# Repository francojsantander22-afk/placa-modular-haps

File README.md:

# main_board_habp

Placa principal (main board) del sistema de adquisición de datos y telemetría para un **globo meteorológico de alta altitud (HABP – High Altitude Balloon Project)**, diseñada en KiCad. Este repositorio contiene el esquemático, el PCB y los archivos de proyecto de la placa que integra el microcontrolador, la red de sensores, el módulo GPS, el enlace LoRa y el sistema de gestión de energía del nodo.

Este proyecto forma parte de una pasantía en CEGA Electrónica, desarrollada por **Franco Santander** y **Lisandro Elmelaj**.

## Descripción general

El objetivo del sistema es recolectar variables físicas del entorno y datos de posicionamiento durante el vuelo de un globo de alta altitud, empaquetarlos de forma eficiente y transmitirlos por radiofrecuencia mediante LoRa, todo en un nodo autónomo capaz de operar en condiciones extremas (hasta ~30 km de altitud, presión menor a 1 kPa y temperaturas de hasta -70 °C).

El sistema completo se organiza en cuatro subsistemas funcionales:

1. Red de sensores
2. Procesamiento de datos y empaquetado
3. Gestión de energía
4. Enlace de comunicaciones (LoRa)

## Hardware

### Microcontrolador

El núcleo del sistema es un microcontrolador de la familia **STM32** (STM32WL55C), montado sobre el módulo **Quectel KG200Z**, que integra de fábrica la etapa de radiofrecuencia LoRa.

### Red de sensores (bus I2C)

Todos los sensores se comunican por I2C (interfaz `I2C3`):

- **BMI270** – IMU de 6 grados de libertad (acelerómetro + giroscopio) con sensor de temperatura interno.
- **SHT21** – Temperatura y humedad ambiente.
- **MS5611** – Presión atmosférica absoluta y temperatura (cálculo de altitud redundante).
- **CMPS2** – Magnetómetro, orientación y azimut respecto al norte magnético.

### Posicionamiento y depuración (UART)

- **ATGM336H (GPS)** vía `USART1`, con recepción por interrupciones sobre un ring buffer de 512 bytes y parsing de tramas NMEA (`GGA`, `VTG`).
- **Consola de telemetría** vía `USART2`, usada como puerto de depuración.

### Gestión de energía

- Celda de litio **18650 en configuración 1S** (3.0 V–4.2 V).
- **BMS** basado en DW01A + FS8205A (protección de sobretensión, subtensión y sobrecorriente).
- Cargador solar **BQ24074** (Texas Instruments), con gestión dinámica de potencia (DPM) entre panel solar y batería.
- Medición de batería por ADC (`PB1`) con divisor resistivo, sobremuestreo y filtro EMA para estimar el estado de carga (SoC).
- Sistema de calefacción para mantener la celda por encima de 0 °C (corte de encendido/apagado en 10 °C / 22 °C).

## Protocolo de comunicaciones: empaquetado TLVPara minimizar el tiempo en el aire (*time-on-air*) del enlace LoRa, el firmware arma un payload binario bajo el esquema **TLV (Type-Length-Value)** en lugar de texto plano, incluyendo únicamente las variables válidas en cada transmisión (por ejemplo, se omiten las coordenadas si el GPS todavía no tiene *fix*).

| Tag | Descripción | Longitud | Formato |
|-----|-------------|----------|---------|
| `0x01` | Hora UTC (GPS) | 3 bytes | Horas, minutos, segundos |
| `0x02` | Coordenadas GPS | 8 bytes | Latitud y longitud (`int32_t`) |
| `0x03` | Altitud GPS | 2 bytes | Metros sobre el nivel del mar |
| `0x04` | Velocidad de desplazamiento | 2 bytes | km/h (×100) |
| `0x05` | Aceleración (IMU) | 6 bytes | Ejes X, Y, Z (`int16_t`) |
| `0x06` | Giroscopio (IMU) | 6 bytes | Ejes X, Y, Z (`int16_t`) |
| `0x07` | Temperatura SHT21 | 2 bytes | °C (×100) |
| `0x08` | Humedad SHT21 | 2 bytes | % (×100) |
| `0x09` | Presión atmosférica (MS5611) | 4 bytes | mbar (×100, `uint32_t`) |
| `0x0B` | Voltaje de batería | 2 bytes | mV (`uint16_t`) |
| `0x0C` | Estado de carga (SoC) | 1 byte | % (0–100) |
| `0x0D` | Azimut (magnetómetro) | 2 bytes | Grados (×100) |
| `0x0E` | Temperatura de batería (DS18B20) | 2 bytes | °C (×100) |
| `0x0F` | Estado del calefactor | 1 byte | Booleano (1 = ON, 0 = OFF) |

El enlace opera en la banda ISM de 915 MHz (configurable a 917.3 MHz), con BW = 125 kHz y SF7 por defecto, gestionado mediante una máquina de estados no bloqueante sobre el secuenciador `UTIL_SEQ`, con ventana de escucha de ACK de 3000 ms tras cada transmisión.

## Diseño de PCB

*Esquemático completo del nodo sensor, capturado de forma jerárquica en KiCad.*

El diseño se realizó en **KiCad**, de forma modular (para poder acoplar directamente los sensores utilizados durante el desarrollo, dejando la versión SMD final para la etapa posterior de integración).

- **2 capas**: capa superior para ruteo de señales y componentes, capa inferior con plano de masa (GND) continuo, plano de alimentación (VCC) y bus I2C.
- Distribución de componentes pensada para minimizar interferencia electromagnética (EMI): el módulo de energía (MPPT) y los conectores de batería en un extremo, el transceptor LoRa/GPS alejado de fuentes de ruido de conmutación.
- Copper pour de GND en las capas exteriores y pistas anchas en la zona del conversor DC-DC (BQ25570) para soportar picos de corriente.
- Orificios de montaje (*mounting holes*) para fijación mecánica al chasis de la sonda.

| Top Layer | Bottom Layer | Top + Bottom |
|:---:|:---:|:---:|
|  |  |  |

### Modelado 3D

| Vista frontal | Vista trasera |
|:---:|:---:|
|  |  |

### Archivos del repositorio

- `prueba1.kicad_pro` / `prueba1.kicad_sch` / `prueba1.kicad_pcb` — proyecto, esquemático y PCB de KiCad.
- `prueba1.kicad_prl` — configuración de proyecto.
- `esquemático.pdf` — esquemático completo exportado.
- `fp-lib-table` / `sym-lib-table` — tablas de librerías de footprints y símbolos.
- `madeinhome.pretty/` — librería de footprints propia.
- `Imagenes/` — renders y capturas del esquemático, capas y modelado 3D de la placa.

## Repositorios relacionados

Este repositorio contiene únicamente el diseño de hardware (PCB). El firmware del proyecto está dividido en repositorios separados:

- **[shield_board_kg200z](https://github.com/francojsantander22-afk/shield_board_kg200z)** — Placa/shield de acople para el módulo Quectel KG200Z.
- **[sensores](https://github.com/francojsantander22-afk/sensores)** — Drivers e integración de la red de sensores (BMI270, SHT21, MS5611, CMPS2).
- **[lora_tx_sensores](https://github.com/francojsantander22-afk/lora_tx_sensores)** — Firmware del nodo transmisor: adquisición de sensores, empaquetado TLV y envío por LoRa.
- **[lora_rx_deco](https://github.com/francojsantander22-afk/lora_rx_deco)** — Firmware del receptor en tierra: recepción del enlace LoRa y decodificación del protocolo TLV.

## Autores

- Franco Santander
- Lisandro Elmelaj

Proyecto desarrollado en el marco de una pasantía en **CEGA Electrónica**.

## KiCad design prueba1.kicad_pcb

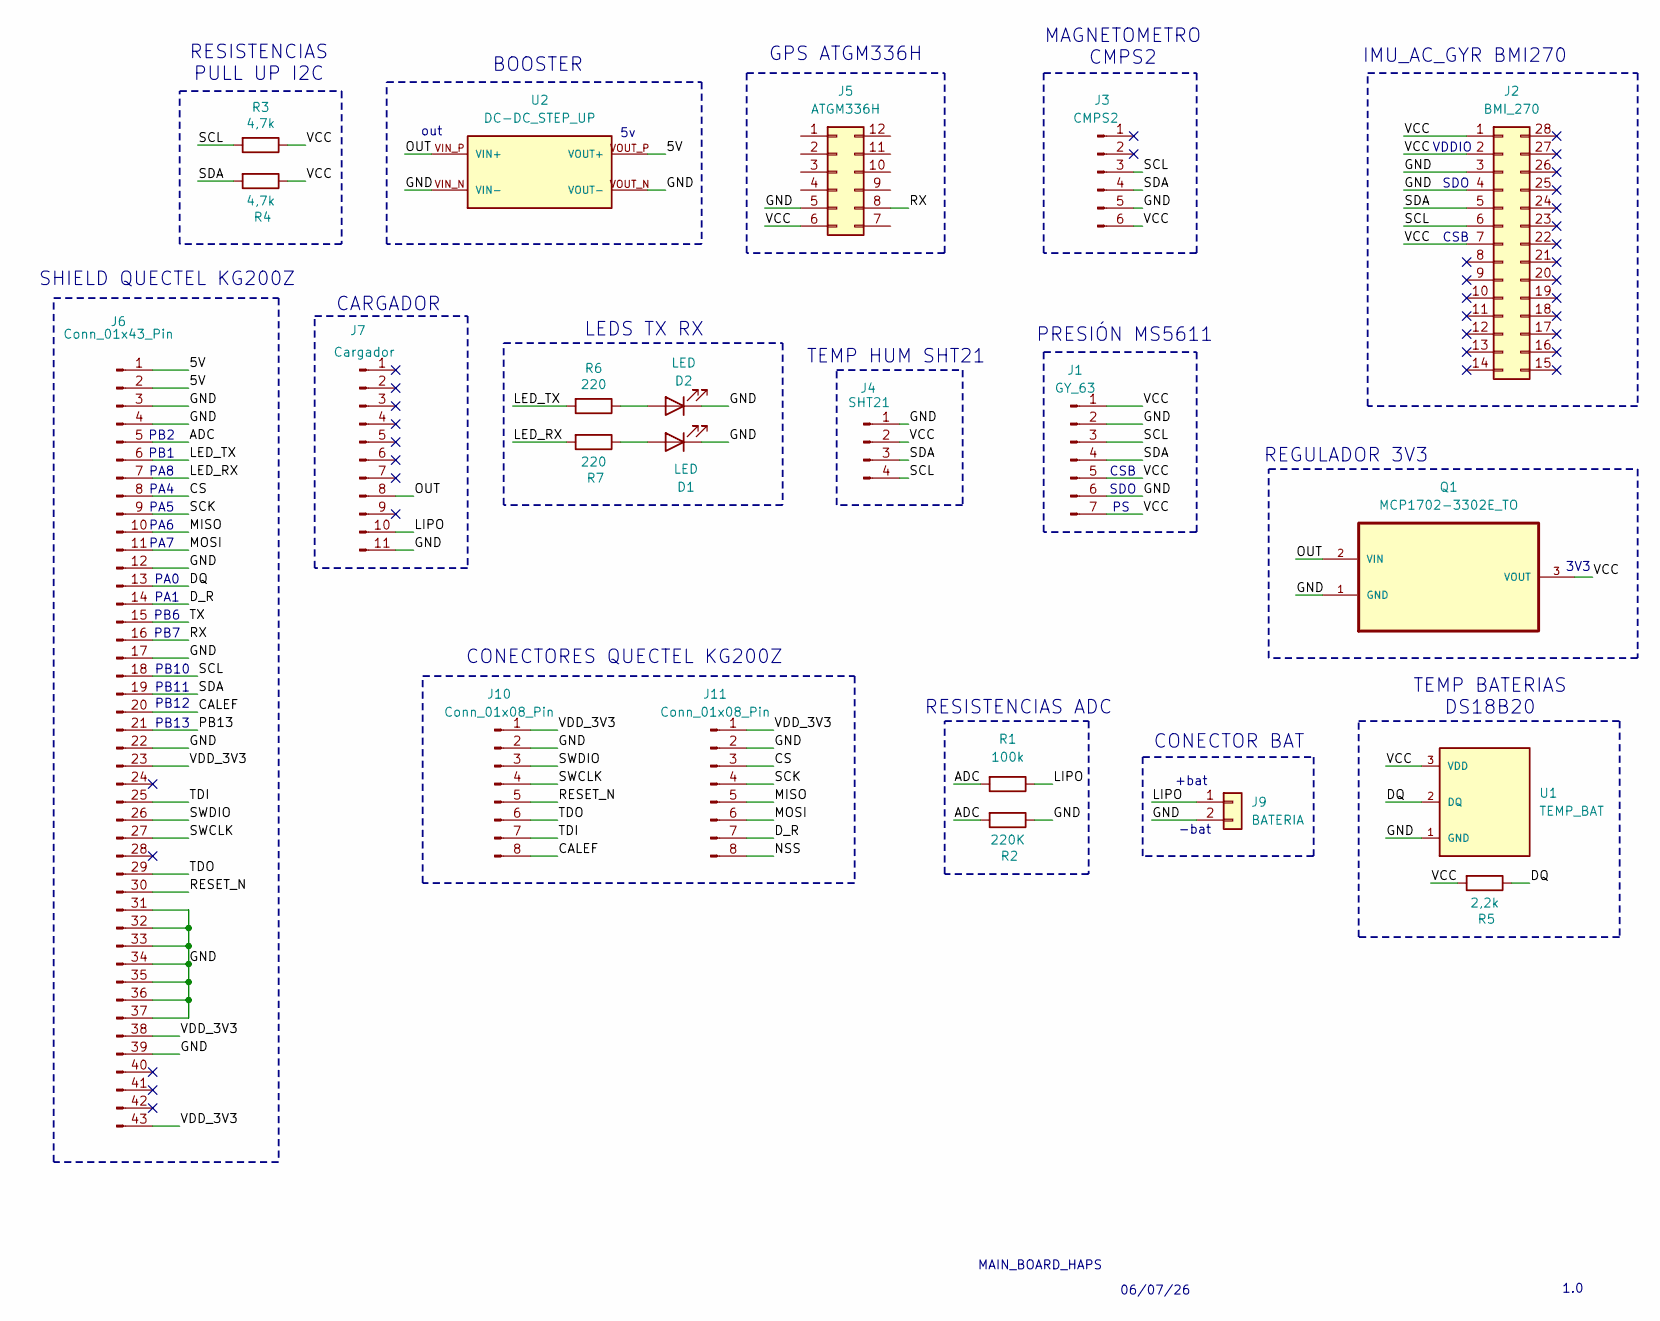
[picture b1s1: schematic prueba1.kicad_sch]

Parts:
D1, D2: LED; LED_D5.0mm
J1: GY_63; PinHeader_1x07_P2.54mm_Vertical
J2: BMI_270
J3: CMPS2
J4: SHT21
J5: ATGM336H
J6: Conn_01x43_Pin; socket_cont
J7: Cargador; cargador
J9: BATERIA; PinHeader_1x02_P2.54mm_Vertical
J10, J11: Conn_01x08_Pin; PinHeader_1x08_P2.54mm_Vertical
Q1: MCP1702-3302E_TO; TO127P254X533-3; MPN MCP1702-3302E/TO
R1: 100k; R_Axial_DIN0207_L6.3mm_D2.5mm_P10.16mm_Horizontal
R2: 220K; R_Axial_DIN0207_L6.3mm_D2.5mm_P10.16mm_Horizontal
R3, R4: 4,7k; R_Axial_DIN0207_L6.3mm_D2.5mm_P10.16mm_Horizontal
R5: 2,2k; R_Axial_DIN0207_L6.3mm_D2.5mm_P10.16mm_Horizontal
R6, R7: 220; R_Axial_DIN0207_L6.3mm_D2.5mm_P10.16mm_Horizontal
U1: TEMP_BAT; TO-92-AMMO
U2: DC-DC_STEP_UP; MODULE_MT3608_DC-DC_STEP_UP_CONVERTER_2A_BOOSTER_MODULE

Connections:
/5V: J6.1, J6.2, U2.VOUT_P (VOUT+)
/ADC: J6.5, R1.2, R2.2
/CALEF: J6.20, J10.8
/CS: J6.8, J11.3
/DQ: J6.13, R5.1, U1.2 (DQ)
/D_R: J6.14, J11.7
/GND: D1.1 (K), D2.1 (K), J1.2, J1.6, J2.3, J2.4, J3.5, J4.1, J5.5, J6.3, J6.4, J6.12, J6.17, J6.22, J6.31, J6.32, J6.33, J6.34, J6.35, J6.36, J6.37, J6.39, J7.11, J9.2, J10.2, J11.2, Q1.1 (GND), R2.1, U1.1 (GND), U2.VIN_N (VIN-), U2.VOUT_N (VOUT-)
/LED_RX: J6.7, R7.2
/LED_TX: J6.6, R6.2
/LIPO: J7.10, J9.1, R1.1
/MISO: J6.10, J11.5
/MOSI: J6.11, J11.6
/NSS: J11.8
/OUT: J7.8, Q1.2 (VIN), U2.VIN_P (VIN+)
/PB13: J6.21
/RESET_N: J6.30, J10.5
/RX: J5.8, J6.16
/SCK: J6.9, J11.4
/SCL: J1.3, J2.6, J3.3, J4.4, J6.18, R3.2
/SDA: J1.4, J2.5, J3.4, J4.3, J6.19, R4.2
/SWCLK: J6.27, J10.4
/SWDIO: J6.26, J10.3
/TDI: J6.25, J10.7
/TDO: J6.29, J10.6
/TX: J6.15
/VCC: J1.1, J1.5, J1.7, J2.1, J2.2, J2.7, J3.6, J4.2, J5.6, Q1.3 (VOUT), R3.1, R4.1, R5.2, U1.3 (VDD)
/VDD_3V3: J6.23, J6.38, J6.43, J10.1, J11.1
unnamed: D1.2 (A), R7.1
unnamed: D2.2 (A), R6.1

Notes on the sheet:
CSB
PA7
REGULADOR 3V3
MAGNETOMETRO CMPS2
+bat
PA1
SHIELD QUECTEL KG200Z
MAIN_BOARD_HAPS
SDO
LEDS TX RX
out
PA8
PA5
PB7
06/07/26
TEMP HUM SHT21
PA0
PB1
CARGADOR
PB10
PB13
RESISTENCIAS PULL UP I2C
PA4
VDDIO
RESISTENCIAS ADC
1.0
PB12
CONECTORES QUECTEL KG200Z
PB6
BOOSTER
IMU_AC_GYR BMI270
GPS ATGM336H
TEMP BATERIAS DS18B20
CONECTOR BAT
3V3
PB11
PB2
PA6
-bat
PRESIÓN MS5611

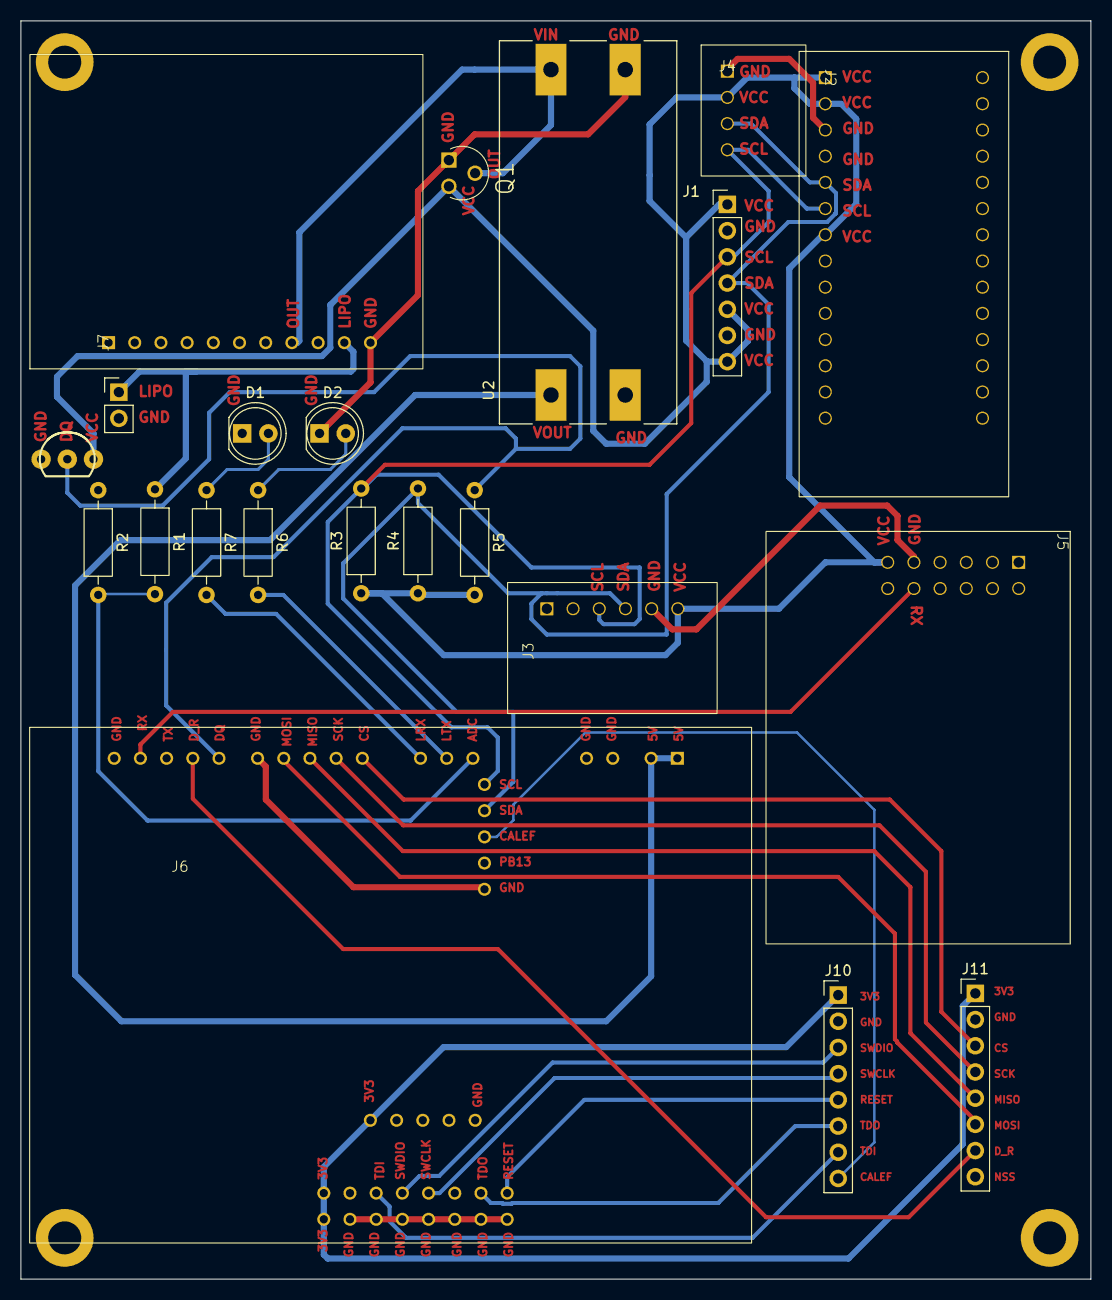
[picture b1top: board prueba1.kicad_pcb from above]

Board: 2 copper layers, 103.8 x 122.0 mm, 22 parts (0 on the bottom side), 26 nets.

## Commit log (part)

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2026-06-26 Esquematico inicial, footprints y modelos 3d
